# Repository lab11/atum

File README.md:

Atum
====

Atum is a ½ inch² drop-in sensor node module designed to enable rapid
prototyping of wireless embedded devices. The core of Atum is a CC2538
SoC with an Arm Cortex M3 and 802.15.4 radio. Atum also includes an
antenna, 512 bytes of non-volatile FRAM memory, an RTC, and a tri-color LED.

Atum is designed to have two different usage patterns. First, three sides
of the device have castellated headers allowing Atum to be directly
soldered onto a carrier PCB. Atum handles all of the computation and
communication while the carrier board supplies power and attaches
sensors or other peripherals. In the second option, Atum can function
as a complete sensor node. On the bottom are pads for a 3.3 V regulator
and a battery. If needed, a peripheral or sensor board can be stacked on
top using the headers as a bridge.

History
-------

Atum is the spiritual successor to
[Epic](http://www.cs.berkeley.edu/~prabal/projects/epic/). It is slightly
smaller, replaces flash with FRAM, adds an RTC, and includes an antenna.
Epic was designed to be highly flexible while still providing the
components that are common on many sensor platforms. In practice, however,
I noticed that only a small subset of the common features were regularly
used and that Epic carrier boards often repeated the same designs. Atum
tries to address this by providing a simplified interface that provides
the features (e.g. SPI, I2C, ADC, GPIO) that sensor boards need.

Name
----

The spelling "Atum" is taken from the ancient Egyptian god of creation,
but finds better connections as a misspelling of "atom", a core building
block of matter, and as the conjoined words "at" and "UM", as Atum
was developed at the University of Michigan.

Usage
-----

The [Contiki](https://github.com/contiki-os/contiki) operating system
supports the CC2538 and this repository contains a Contiki platform
for Atum. The Contiki platform provides drivers for the peripherals
on Atum and their wiring to the CC2538. See `CONTIKI.md` for more info.

PCB
---

Atum is currently pannelized 40 to a panel. They are designed to be 1mm thick
with castellations on the edge. See `hardware/atum` for board files and
gerbers.

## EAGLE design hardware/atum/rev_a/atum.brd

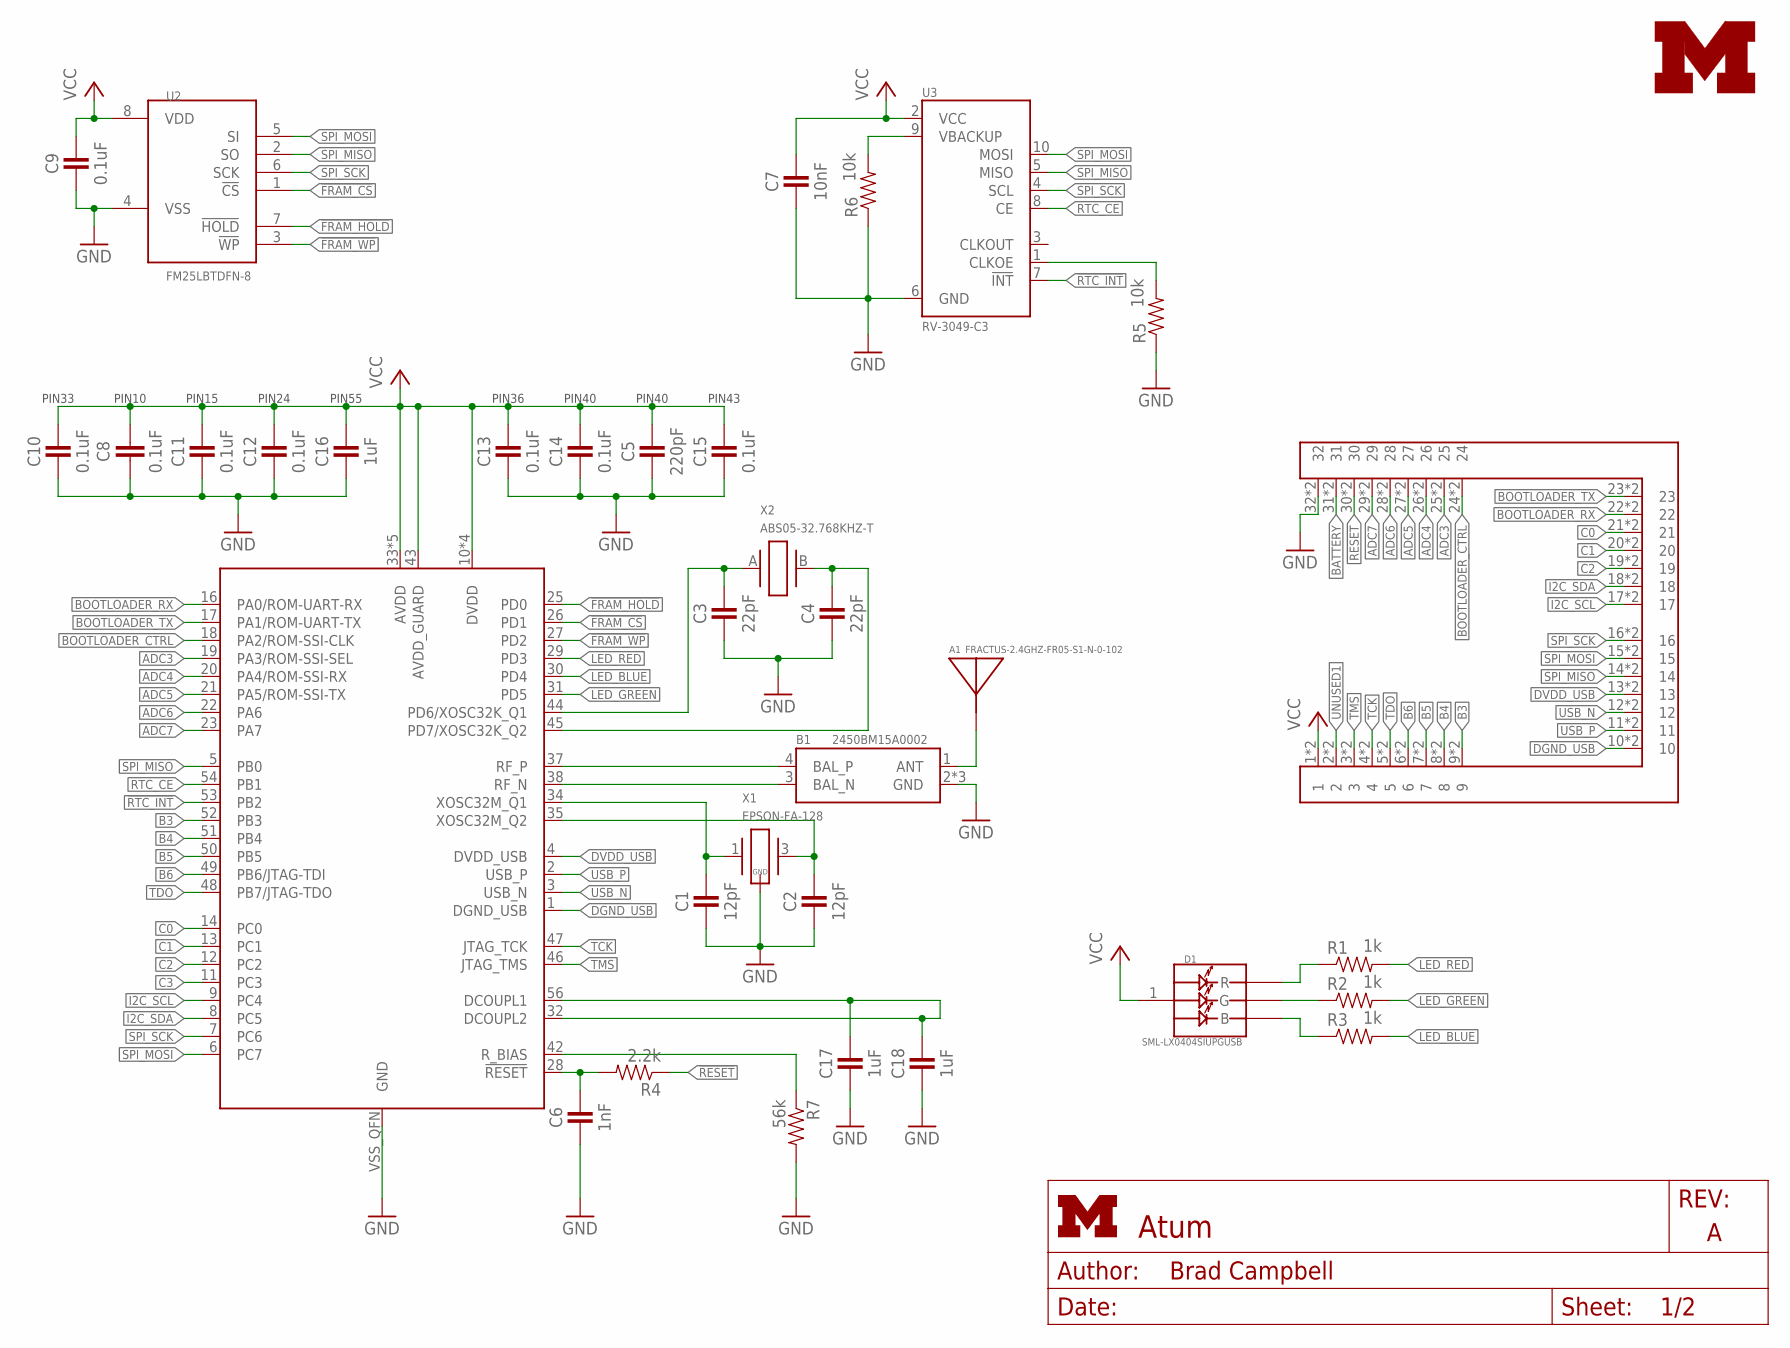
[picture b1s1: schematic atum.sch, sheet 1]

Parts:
A1: FRACTUS-2.4GHZ-FR05-S1-N-0-102; FRACTUS-ANTENNA-FR05-S1-N-0-102
B1: 2450BM15A0002; 2450BM
C1, C2: 12pF; 0402_CAP
C3, C4: 22pF; 0402_CAP
C5: 220pF; 0402_CAP
C6: 1nF; 0402_CAP
C7: 10nF; 0402_CAP
C8: 0.1uF; C0201
C9, C10, C11, C12, C13, C14, C15: 0.1uF; 0402_CAP
C16, C17, C18: 1uF; 0402_CAP
D1: SML-LX0404SIUPGUSB; 1MM_SQ_4PAD
J3: ATUM-HEADER
LOGO1: UMICH_SOLID_TINY; UMICH_SOLID_50MIL
R1, R2, R3: 1k; 0402_RES
R4: 2.2k; 0402_RES
R5, R6: 10k; 0402_RES
R7: 56k; 0402_RES
U1: CC2538; S-PVQFN-N56
U2: FM25LBTDFN-8; TDFN-8; DIGIKEY FM25L04B-DGRA-ND
U3: RV-3049-C3; MICRO-CRYSTAL-C3
X1: EPSON-FA-128; FA-128
X2: ABS05-32.768KHZ-T; ABS05

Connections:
!FRAM_CS: U1.26 (PD1), U2.1 (!CS)
!FRAM_HOLD: U1.25 (PD0), U2.7 (!HOLD)
!FRAM_WP: U1.27 (PD2), U2.3 (!WP)
!RESET: J3.30, J3.30B (30), R4.1
!RTC_INT: U1.53 (PB2), U3.7 (!INT)
ADC3: J3.25, J3.25B (25), U1.19 (PA3/ROM-SSI-SEL)
ADC4: J3.26, J3.26B (26), U1.20 (PA4/ROM-SSI-RX)
ADC5: J3.27, J3.27B (27), U1.21 (PA5/ROM-SSI-TX)
ADC6: J3.28, J3.28B (28), U1.22 (PA6)
ADC7: J3.29, J3.29B (29), U1.23 (PA7)
ANTENNA: A1.1, B1.1 (ANT)
B3: J3.9, J3.9B (9), U1.52 (PB3)
B4: J3.8, J3.8B (8), U1.51 (PB4)
B5: J3.7, J3.7B (7), U1.50 (PB5)
B6: J3.6, J3.6B (6), U1.49 (PB6/JTAG-TDI)
BATTERY: J3.31, J3.31B (31); also elsewhere on the board
BOOTLOADER_CTRL: J3.24, J3.24B (24), U1.18 (PA2/ROM-SSI-CLK)
BOOTLOADER_RX: J3.22, J3.22B (22), U1.16 (PA0/ROM-UART-RX)
BOOTLOADER_TX: J3.23, J3.23B (23), U1.17 (PA1/ROM-UART-TX)
C0: J3.21, J3.21B (21), U1.14 (PC0)
C1: J3.20, J3.20B (20), U1.13 (PC1)
C2: J3.19, J3.19B (19), U1.12 (PC2)
C3: U1.11 (PC3)
DGND_USB: J3.10, J3.10B (10), U1.1 (DGND_USB)
DVDD_USB: J3.13, J3.13B (13), U1.4 (DVDD_USB)
GND: B1.2 (GND), B1.5 (GND), B1.6 (GND), C1.2, C2.2, C3.2, C4.2, C5.2, C6.2, C7.2, C8.2, C9.2, C10.2, C11.2, C12.2, C13.2, C14.2, C15.2, C16.2, C17.2, C18.2, J3.32, J3.32B (32), R5.1, R6.1, R7.2, U1.VSS_QFN (GND), U2.4 (VSS), U3.6 (GND), X1.2 (GND), X1.4 (GND); also elsewhere on the board
I2C_SCL: J3.17, J3.17B (17), U1.9 (PC4)
I2C_SDA: J3.18, J3.18B (18), U1.8 (PC5)
LED_BLUE: R3.2, U1.30 (PD4)
LED_GREEN: R2.2, U1.31 (PD5)
LED_RED: R1.2, U1.29 (PD3)
unnamed: C6.1, R4.2, U1.28 (!RESET)
unnamed: C3.1, U1.44 (PD6/XOSC32K_Q1), X2.A (1)
unnamed: D1.2 (R), R1.1
unnamed: R7.1, U1.42 (R_BIAS)
unnamed: C1.1, U1.34 (XOSC32M_Q1), X1.1
unnamed: C2.1, U1.35 (XOSC32M_Q2), X1.3 (2)
unnamed: D1.4 (G), R2.1
unnamed: D1.3 (B), R3.1
unnamed: C4.1, U1.45 (PD7/XOSC32K_Q2), X2.B (2)
unnamed: R6.2, U3.9 (VBACKUP)
unnamed: C17.1, C18.1, U1.32 (DCOUPL2), U1.56 (DCOUPL1)
unnamed: R5.2, U3.1 (CLKOE)
RF_N: B1.3 (BAL_N), U1.38 (RF_N)
RF_P: B1.4 (BAL_P), U1.37 (RF_P)
RTC_CE: U1.54 (PB1), U3.8 (CE)
SPI_MISO: J3.14, J3.14B (14), U1.5 (PB0), U2.2 (SO), U3.5 (MISO)
SPI_MOSI: J3.15, J3.15B (15), U1.6 (PC7), U2.5 (SI), U3.10 (MOSI)
SPI_SCK: J3.16, J3.16B (16), U1.7 (PC6), U2.6 (SCK), U3.4 (SCL)
TCK: J3.4, J3.4B (4), U1.47 (JTAG_TCK)
TDO: J3.5, J3.5B (5), U1.48 (PB7/JTAG-TDO)
TMS: J3.3, J3.3B (3), U1.46 (JTAG_TMS)
UNUSED1: J3.2, J3.2B (2)
USB_N: J3.12, J3.12B (12), U1.3 (USB_N)
USB_P: J3.11, J3.11B (11), U1.2 (USB_P)
VCC: C5.1, C7.1, C8.1, C9.1, C10.1, C11.1, C12.1, C13.1, C14.1, C15.1, C16.1, D1.1 (VDD), J3.1, J3.1B (1), U1.10 (DVDD), U1.15 (DVDD), U1.24 (DVDD), U1.33 (AVDD), U1.36 (AVDD), U1.39 (AVDD), U1.40 (AVDD), U1.41 (AVDD), U1.43 (AVDD_GUARD), U1.55 (DVDD), U2.8 (VDD), U3.2 (VCC); also elsewhere on the board

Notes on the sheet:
PIN10
PIN15
PIN24
PIN55
PIN33
PIN36
PIN40
PIN43

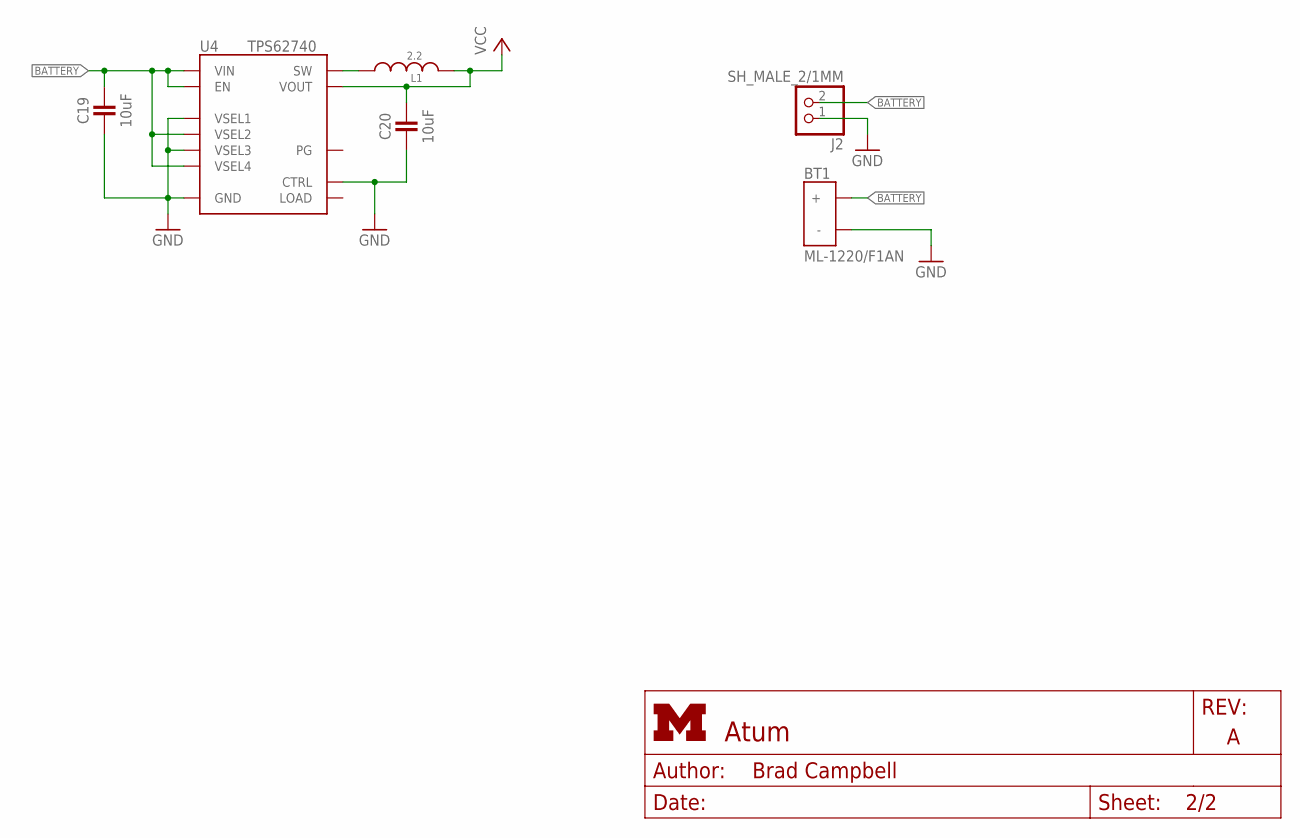
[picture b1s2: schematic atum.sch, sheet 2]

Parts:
BT1: ML-1220/F1AN; ML-1220/F1BN
C19, C20: 10uF; 0603_CAP; DIGIKEY 490-7316-1-ND
J2: SH_MALE_2/1MM; SH-1X2/1MM
L1: 2.2; MIPSZ201D
U4: TPS62740; R-PWSON-12

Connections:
BATTERY: BT1.POS (+), C19.1, J2.2, U4.1 (VIN), U4.8 (VSEL4), U4.10 (VSEL2), U4.12 (EN); also elsewhere on the board
GND: BT1.NEG (-), C19.2, C20.2, J2.1, U4.3 (GND), U4.4 (CTRL), U4.9 (VSEL3), U4.11 (VSEL1), U4.NC (GND); also elsewhere on the board
unnamed: L1.1, U4.2 (SW)
VCC: C20.1, L1.2, U4.5 (VOUT); also elsewhere on the board

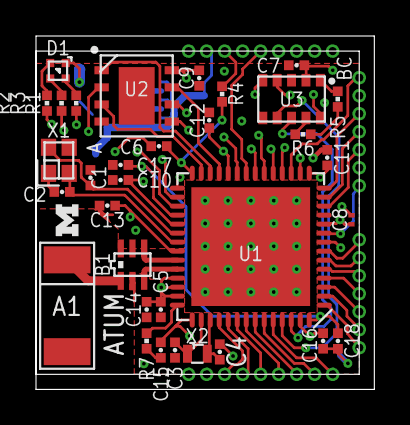
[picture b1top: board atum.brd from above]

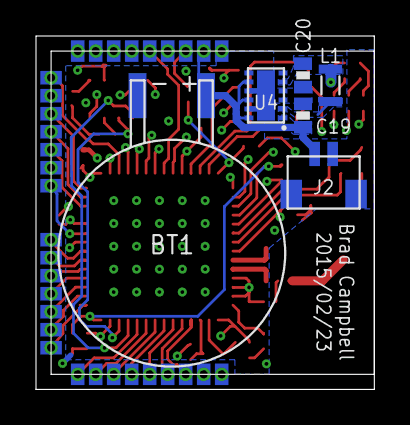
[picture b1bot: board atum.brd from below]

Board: 4 copper layers, 18.8 x 19.6 mm, 41 parts (6 on the bottom side), 56 nets.

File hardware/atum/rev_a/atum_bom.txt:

# Bill of Materials
# Converted from atum_bom.xlsx
# Generated by bom_to_text.py

Qty  Value                           Device                          Package                          Parts                             Description                                                   DIGIKEY           MOUSER               NEWARK   RICHARDSON_RFPD
1    FRACTUS-2.4GHZ-FR05-S1-N-0-102  FRACTUS-2.4GHZ-FR05-S1-N-0-102  FRACTUS-ANTENNA-FR05-S1-N-0-102  A1                                Fractus Compact Reach XtendTM chip antenna                                                                    FR05-S1-N-0102B
1    2450BM15A0002                   2450BM15A0002                   2450BM                           B1                                BALUN JTI MATCHED ZIGBEE                                      712-1536-1-ND     609-2450BM15A0002E   41T1684  
1    ML-1220/F1AN                    ML-1220/F1AN                    ML-1220/F1BN                     BT1                               BATTERY LITH 3V RECHARGE PC PINS                              P663-ND           658-ML-1220/F1BN              
2    12pF                            CAPACITOR                       0402_CAP                         C1, C2                            0402 Capacitor                                                445-1236-1-ND                          90R7560  
2    22pF                            CAPACITOR                       0402_CAP                         C3, C4                            0402 Capacitor                                                490-5868-1-ND                          48W5745  
1    220pF                           CAPACITOR                       0402_CAP                         C5                                0402 Capacitor                                                445-1251-1-ND                          55T0065  
1    1nF                             CAPACITOR                       0402_CAP                         C6                                0402 Capacitor                                                445-2651-1-ND                          90R7554  
1    10nF                            CAPACITOR                       0402_CAP                         C7                                0402 Capacitor                                                445-1260-1-ND                          90R7604  
1    0.1uF                           C-EUC0201                       0201_CAP                         C8                                0201 Capacitor                                                445-1796-1-ND                          90R7553  
7    0.1uF                           CAPACITOR                       0402_CAP                         C9, C10, C11, C12, C13, C14, C15  0402 Capacitor                                                445-1265-1-ND                          87R3259  
3    1uF                             CAPACITOR                       0402_CAP                         C16, C17, C18                     0402 Capacitor                                                445-4998-1-ND                          90R7580  
2    10uF                            CAPACITOR0603_CAP               0603_CAP                         C19, C20                          CAP CER 10UF 6.3V 20% X5R 0603                                490-7316-1-ND                                   
1    SML-LX0404SIUPGUSB              SML-LX0404SIUPGUSB              1MM_SQ_4PAD                      D1                                1mm^2 RGB LED                                                 67-2125-1-ND      696-LX0404SIUPGUSB   23T0583  
1    ATUM-HEADER                     ATUM-HEADER                     ATUM-HEADER                      J1                                                                                                                                              
1    SH_MALE_2/1MM                   SH_MALE_2/1MM                   SH-1X2/1MM                       J2                                1.0mm pitch/Disconnectable Crimp style connectors             455-1788-2-ND                          26P0950  
1    2.2uH                           MIPSZ2012D                      MIPSZ201D                        L1                                FDK Multi-layer Power Inductor (Very Small Type)                                                              
3    1k                              RESISTOR                        0402_RES                         R1, R2, R3                        Resistor                                                      RHM1.0KCECT-ND                                  
1    2.2k                            RESISTOR                        0402_RES                         R4                                Resistor                                                      RHM2.2KCECT-ND                                  
2    10k                             RESISTOR                        0402_RES                         R5, R6                            Resistor                                                      RHM10KCECT-ND                                   
1    56k                             RESISTOR                        0402_RES                         R7                                Resistor                                                      RHM56KBHCT-ND                                   
1    CC2538                          CC2538                          S-PVQFN-N56                      U1                                A Powerful System-On-Chip for 2.4-GHz IEEE 802.15.4, 6LoWPAN  296-35797-1-ND    595-CC2538SF53RTQT   87W7713  
1    FM25LBTDFN-8                    FM25LBTDFN-8                    TDFN-8                           U2                                IC FRAM 4KBIT 10MHZ 8SOIC                                     FM25L04B-DGRA-ND  877-FM25L04B-DG               
1    RV-3049-C3                      RV-3049-C3                      MICRO-CRYSTAL-C3                 U3                                Ultra miniature Real-Time-Clock Module                                                               09X0513  
1    TPS62740                        TPS62740                        R-PWSON-12                       U4                                360nA Step Down Converter for Low Power Applications          296-37134-1-ND    595-TPS62740DSST     27X9745  
1    EPSON-FA-128                    EPSON-FA-128                    FA-128                           X1                                MHz RANGE CRYSTAL UNIT                                        SER3800CT-ND      732-FA128-32F20X-K3           
1    ABS05-32.768KHZ-T               ABS05-32.768KHZ-T               ABS05                            X2                                32.768kHz Crystal                                             535-11899-1-ND    815-ABS05-32.768K-T  24W8430

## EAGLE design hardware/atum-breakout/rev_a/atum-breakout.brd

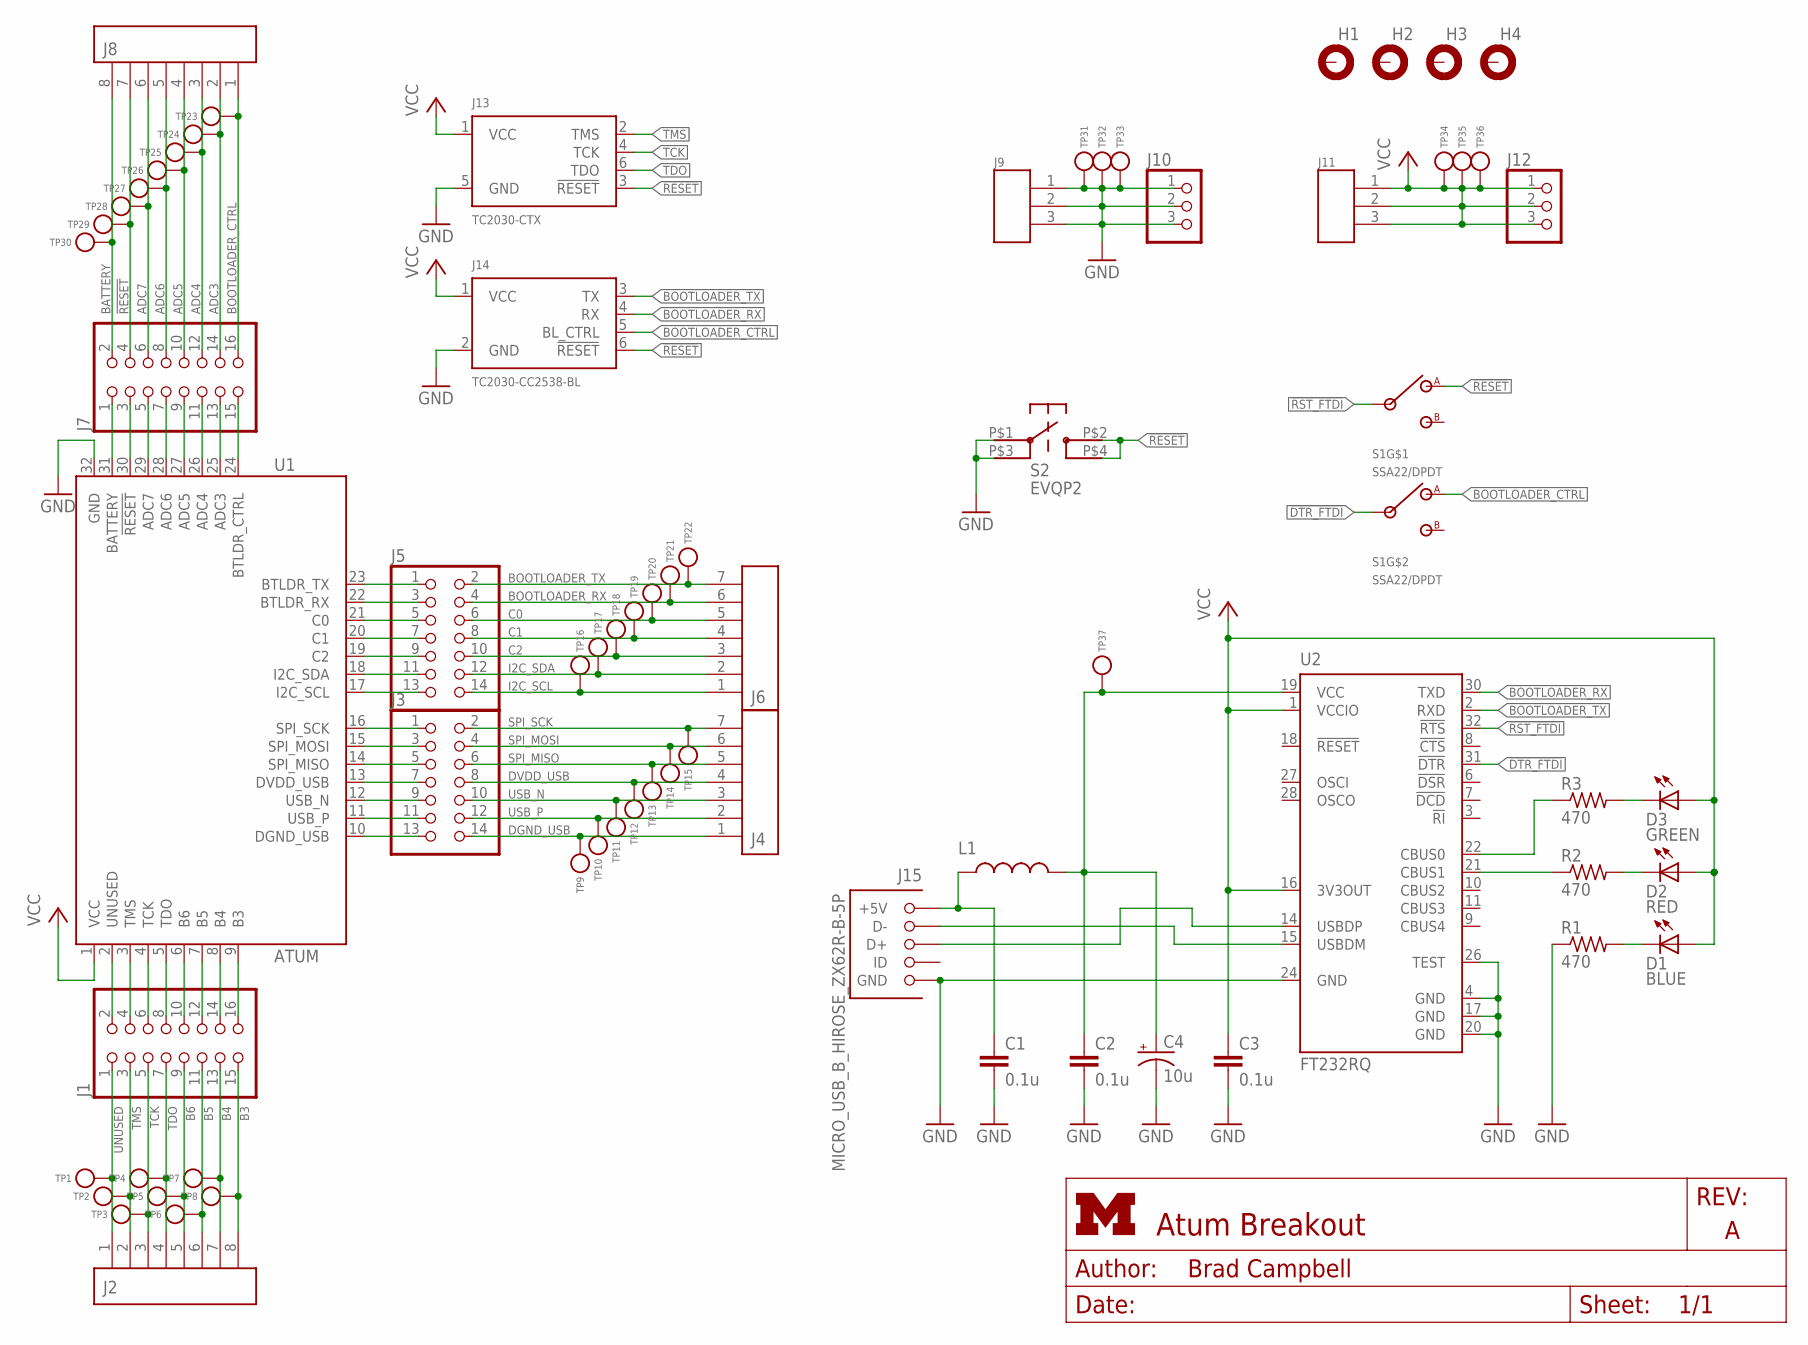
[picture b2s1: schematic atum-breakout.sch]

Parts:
C1, C2, C3: 0.1u; C0603; DIGIKEY 445-1316-1-ND
C4: 10u; EIA3216; DIGIKEY 478-1655-1-ND
D1: BLUE; LED-0603
D2: RED; LED-0603
D3: GREEN; LED-0603
H1, H2, H3, H4: MOUNT-PAD-ROUND3.2; 3,2-PAD
J1, J7: PINHD-2X8; 2X08; DIGIKEY 609-3364-ND
J2, J8: SCREW-TERMINAL_8_0.100; CONN_BLOCK_8
J3, J5: PINHD-2X7; 2X07; DIGIKEY 609-3491-ND
J4, J6: SCREW-TERMINAL_7_0.100; CONN_BLOCK_7
J9, J11: SCREW-TERMINAL_3_0.100; CONN_BLOCK_3
J10, J12: PINHD-1X3; 1X03
J13: TC2030-CTX; TC2030-IDC
J14: TC2030-CC2538-BL; TC2030-IDC
J15: MICRO_USB_B_HIROSE_ZX62R-B-5P; USB_MICRO_B-HIROSE-ZX62R-B-5P; MOUSER 798-ZX62R-B-5P
L1: INDUCTOR0603; 0603; DIGIKEY 240-2373-1-ND
R1, R2, R3: 470; R0603
S1: SSA22/DPDT; DIGIKEY 450-1604-ND
S2: EVQP2; DIGIKEY P11084SCT-ND
TP1, TP2, TP3, TP4, TP5, TP6, TP7, TP8, TP9, TP10, TP11, TP12, TP13, TP14, TP15, TP16, TP17, TP18, TP19, TP20, TP21, TP22, TP23, TP24, TP25, TP26, TP27, TP28, TP29, TP30, TP31, TP32, TP33, TP34, TP35, TP36, TP37: TEST_POINT_0.040IN; TESTPOINT_0.040IN
U1: ATUM
U2: FT232RQ; QFN32; DIGIKEY 768-1008-1-ND

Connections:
!DTR_FTDI: S1.COM2 (2), U2.31 (!DTR)
!RESET: J7.3, J7.4, J8.7, J13.3 (!RESET), J14.6 (!RESET), S1.A1 (1), S2.P$2, S2.P$4, TP29.TESTPOINT, U1.30 (!RESET)
!RST_FTDI: S1.COM1 (2), U2.32 (!RTS)
ADC3: J7.13, J7.14, J8.2, TP24.TESTPOINT, U1.25 (ADC3)
ADC4: J7.11, J7.12, J8.3, TP25.TESTPOINT, U1.26 (ADC4)
ADC5: J7.9, J7.10, J8.4, TP26.TESTPOINT, U1.27 (ADC5)
ADC6: J7.7, J7.8, J8.5, TP27.TESTPOINT, U1.28 (ADC6)
ADC7: J7.5, J7.6, J8.6, TP28.TESTPOINT, U1.29 (ADC7)
B3: J1.15, J1.16, J2.8, TP8.TESTPOINT, U1.9 (B3)
B4: J1.13, J1.14, J2.7, TP7.TESTPOINT, U1.8 (B4)
B5: J1.11, J1.12, J2.6, TP6.TESTPOINT, U1.7 (B5)
B6: J1.9, J1.10, J2.5, TP5.TESTPOINT, U1.6 (B6)
BATTERY: J7.1, J7.2, J8.8, TP30.TESTPOINT, U1.31 (BATTERY)
BOOTLOADER_CTRL: J7.15, J7.16, J8.1, J14.5 (BL_CTRL), S1.A2 (1), TP23.TESTPOINT, U1.24 (BTLDR_CTRL)
BOOTLOADER_RX: J5.3, J5.4, J6.6, J14.4 (RX), TP21.TESTPOINT, U1.22 (BTLDR_RX), U2.30 (TXD)
BOOTLOADER_TX: J5.1, J5.2, J6.7, J14.3 (TX), TP22.TESTPOINT, U1.23 (BTLDR_TX), U2.2 (RXD)
C0: J5.5, J5.6, J6.5, TP20.TESTPOINT, U1.21 (C0)
C1: J5.7, J5.8, J6.4, TP19.TESTPOINT, U1.20 (C1)
C2: J5.9, J5.10, J6.3, TP18.TESTPOINT, U1.19 (C2)
DGND_USB: J3.13, J3.14, J4.1, TP9.TESTPOINT, U1.10 (DGND_USB)
DVDD_USB: J3.7, J3.8, J4.4, TP12.TESTPOINT, U1.13 (DVDD_USB)
GND: C1.2, C2.2, C3.2, C4.C (-), J9.1, J9.2, J9.3, J10.1, J10.2, J10.3, J13.5 (GND), J14.2 (GND), J15.5 (GND), R1.1, S2.P$1, S2.P$3, TP31.TESTPOINT, TP32.TESTPOINT, TP33.TESTPOINT, U1.32 (GND), U2.4 (GND), U2.17 (GND), U2.20 (GND), U2.24 (GND), U2.26 (TEST)
I2C_SCL: J5.13, J5.14, J6.1, TP16.TESTPOINT, U1.17 (I2C_SCL)
I2C_SDA: J5.11, J5.12, J6.2, TP17.TESTPOINT, U1.18 (I2C_SDA)
unnamed: R3.1, U2.22 (CBUS0)
unnamed: D2.C, R2.2
unnamed: J15.2 (D-), U2.15 (USBDM)
unnamed: J15.3 (D+), U2.14 (USBDP)
unnamed: R2.1, U2.21 (CBUS1)
unnamed: C2.1, C4.A (+), L1.2, TP37.TESTPOINT, U2.19 (VCC)
unnamed: D3.C, R3.2
unnamed: D1.C, R1.2
SPI_MISO: J3.5, J3.6, J4.5, TP13.TESTPOINT, U1.14 (SPI_MISO)
SPI_MOSI: J3.3, J3.4, J4.6, TP14.TESTPOINT, U1.15 (SPI_MOSI)
SPI_SCK: J3.1, J3.2, J4.7, TP15.TESTPOINT, U1.16 (SPI_SCK)
TCK: J1.5, J1.6, J2.3, J13.4 (TCK), TP3.TESTPOINT, U1.4 (TCK)
TDO: J1.7, J1.8, J2.4, J13.6 (TDO), TP4.TESTPOINT, U1.5 (TDO)
TMS: J1.3, J1.4, J2.2, J13.2 (TMS), TP2.TESTPOINT, U1.3 (TMS)
UNUSED: J1.1, J1.2, J2.1, TP1.TESTPOINT, U1.2 (UNUSED)
USB5V: C1.1, J15.1 (+5V), L1.1
USB_N: J3.9, J3.10, J4.3, TP11.TESTPOINT, U1.12 (USB_N)
USB_P: J3.11, J3.12, J4.2, TP10.TESTPOINT, U1.11 (USB_P)
VCC: C3.1, D1.A, D2.A, D3.A, J11.1, J11.2, J11.3, J12.1, J12.2, J12.3, J13.1 (VCC), J14.1 (VCC), TP34.TESTPOINT, TP35.TESTPOINT, TP36.TESTPOINT, U1.1 (VCC), U2.1 (VCCIO), U2.16 (3V3OUT)

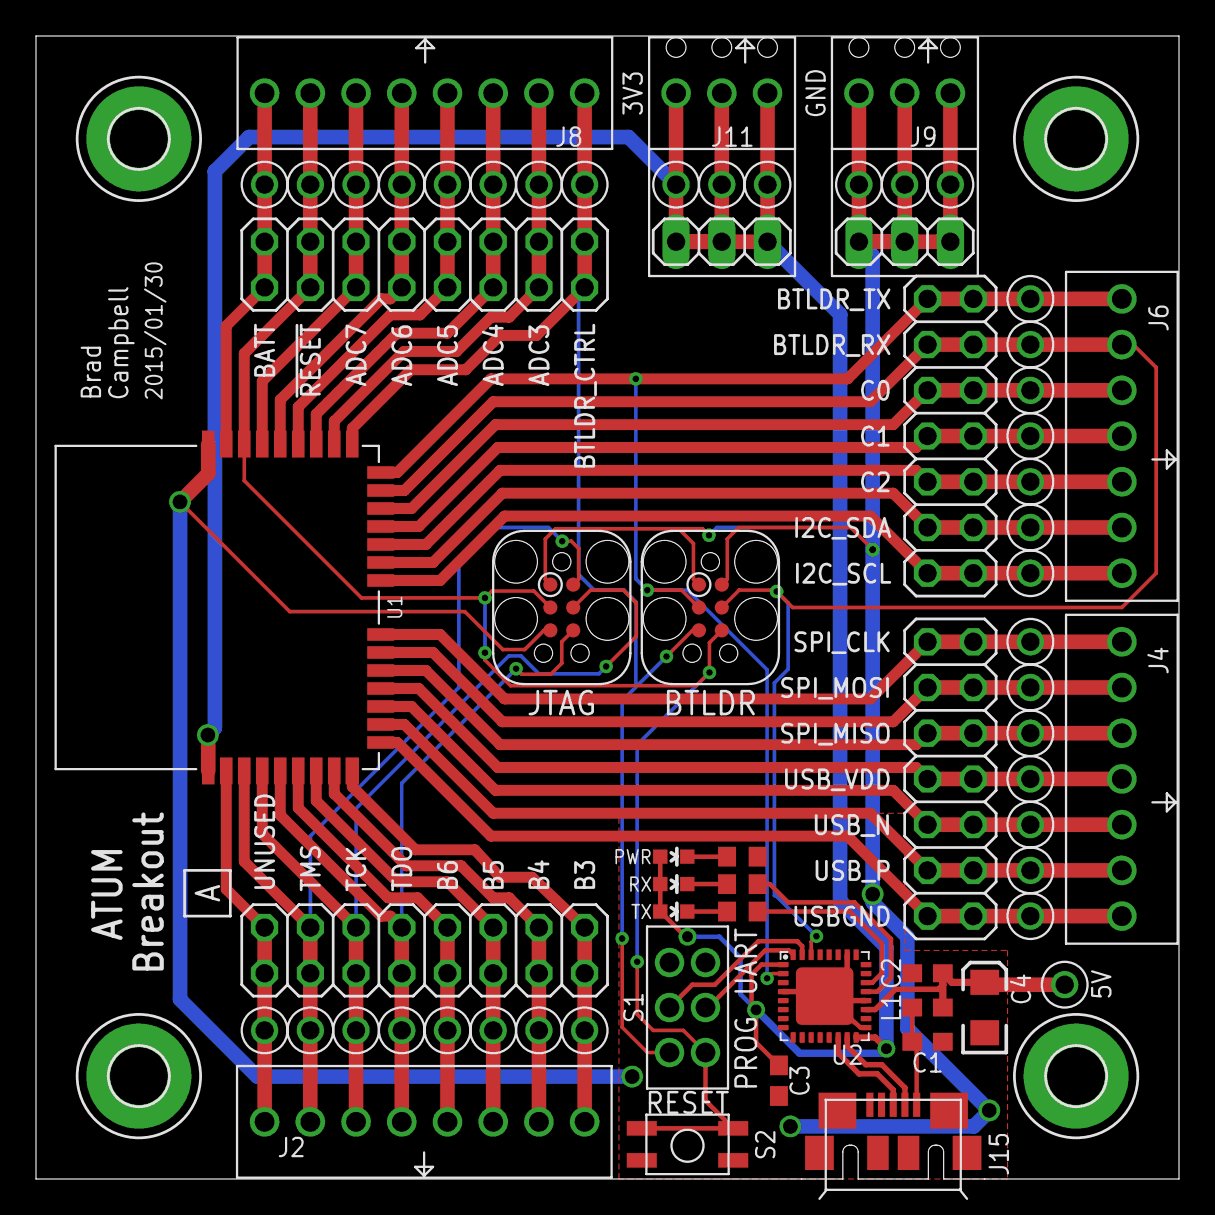
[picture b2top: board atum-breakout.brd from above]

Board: 2 copper layers, 63.5 x 63.5 mm, 71 parts (0 on the bottom side), 43 nets.

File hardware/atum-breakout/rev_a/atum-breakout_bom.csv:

# Bill of Materials
# Converted from atum-breakout_bom.xlsx
# Generated by bom_to_text.py

Qty,Value,Device,Package,Parts,Description,DIGIKEY,MOUSER,NEWARK
3,0.1u,C-EUC0603,C0603,"C1, C2, C3","CAPACITOR, European symbol",445-1316-1-ND,810-C1608X7R1E104K,
1,10u,CAP_POL1206,EIA3216,C4,Capacitor Polarized,478-1655-1-ND,581-TAJA106K016R,
1,BLUE,LED0603,LED-0603,D1,LEDs,,,
1,RED,LED0603,LED-0603,D2,LEDs,,,
1,GREEN,LED0603,LED-0603,D3,LEDs,,,
2,,PINHD-2X8,2X08,"J1, J7",PIN HEADER,609-3364-ND,649-68602-116HLF,20M2833
2,SCREW-TERMINAL_8_0.100,SCREW-TERMINAL_8_0.100,CONN_BLOCK_8,"J2, J8",8x 0.100 in screw terminal block,277-1279-ND,651-1725711,71C4111
2,,PINHD-2X7,2X07,"J3, J5",PIN HEADER,609-3491-ND,649-67996-114HLF,30M1973
2,SCREW-TERMINAL_7_0.100,SCREW-TERMINAL_7_0.100,CONN_BLOCK_7,"J4, J6",7x 0.100 in screw terminal block,277-1278-ND,651-1725708,14X4980
2,SCREW-TERMINAL_3_0.100,SCREW-TERMINAL_3_0.100,CONN_BLOCK_3,"J9, J11",3x 0.100 in screw terminal block,277-1274-ND,651-1725669,71C4108
2,,PINHD-1X3,1X03,"J10, J12",PIN HEADER,609-3461-ND,649-68000-103HLF,88K1775
1,MICRO_USB_B_HIROSE_ZX62R-B-5P,MICRO_USB_B_HIROSE_ZX62R-B-5P,USB_MICRO_B-HIROSE-ZX62R-B-5P,J15,USB Micro B Connector,H11574CT-ND,798-ZX62R-B-5P,69W0714
1,,INDUCTOR0603,L0603,L1,Inductors,240-2373-1-ND,875-MI0603K300R-10,
3,470,R-US_R0603,R0603,"R1, R2, R3","RESISTOR, American symbol",,,
1,SSA22/DPDT,SSA22/DPDT,SSA22/DPDT,S1,SW SLIDE DPDT 2POS SSA SER 30V,450-1604-ND,506-SSA22,50F5561
1,EVQP2,EVQP2,EVQP2,S2,,P11084SCT-ND,667-EVQ-P2K02Q,
37,TEST_POINT_0.040IN,TEST_POINT_0.040IN,TESTPOINT_0.040IN,TP1-TP37,0.040in Test Point,5001K-ND,534-5001,
1,ATUM,ATUM,ATUM,U1,Atum sensorboard prototyping module.,,,
1,FT232RQ,FT232RQ,QFN32,U2,FTDI USB,768-1008-1-ND,895-FT232RQ,91K9919

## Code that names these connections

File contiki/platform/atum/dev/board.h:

/*
 * Copyright (c) 2012, Texas Instruments Incorporated - http://www.ti.com/
 * All rights reserved.
 *
 * Redistribution and use in source and binary forms, with or without
 * modification, are permitted provided that the following conditions
 * are met:
 * 1. Redistributions of source code must retain the above copyright
 *    notice, this list of conditions and the following disclaimer.
 * 2. Redistributions in binary form must reproduce the above copyright
 *    notice, this list of conditions and the following disclaimer in the
 *    documentation and/or other materials provided with the distribution.
 *
 * 3. Neither the name of the copyright holder nor the names of its
 *    contributors may be used to endorse or promote products derived
 *    from this software without specific prior written permission.
 *
 * THIS SOFTWARE IS PROVIDED BY THE COPYRIGHT HOLDERS AND CONTRIBUTORS
 * ``AS IS'' AND ANY EXPRESS OR IMPLIED WARRANTIES, INCLUDING, BUT NOT
 * LIMITED TO, THE IMPLIED WARRANTIES OF MERCHANTABILITY AND FITNESS
 * FOR A PARTICULAR PURPOSE ARE DISCLAIMED.  IN NO EVENT SHALL THE
 * COPYRIGHT HOLDER OR CONTRIBUTORS BE LIABLE FOR ANY DIRECT, INDIRECT,
 * INCIDENTAL, SPECIAL, EXEMPLARY, OR CONSEQUENTIAL DAMAGES
 * (INCLUDING, BUT NOT LIMITED TO, PROCUREMENT OF SUBSTITUTE GOODS OR
 * SERVICES; LOSS OF USE, DATA, OR PROFITS; OR BUSINESS INTERRUPTION)
 * HOWEVER CAUSED AND ON ANY THEORY OF LIABILITY, WHETHER IN CONTRACT,
 * STRICT LIABILITY, OR TORT (INCLUDING NEGLIGENCE OR OTHERWISE)
 * ARISING IN ANY WAY OUT OF THE USE OF THIS SOFTWARE, EVEN IF ADVISED
 * OF THE POSSIBILITY OF SUCH DAMAGE.
 */
/** \addtogroup cc2538
 * @{
 *
 * \defgroup cc2538-smartrf SmartRF06EB Peripherals
 *
 * Defines related to the SmartRF06EB
 *
 * This file provides connectivity information on LEDs, Buttons, UART and
 * other SmartRF peripherals
 *
 * Notably, PC0 is used to drive LED1 as well as the USB D+ pullup. Therefore
 * when USB is enabled, LED1 can not be driven by firmware.
 *
 * This file can be used as the basis to configure other platforms using the
 * cc2538 SoC.
 * @{
 *
 * \file
 * Header file with definitions related to the I/O connections on the TI
 * SmartRF06EB
 *
 * \note   Do not include this file directly. It gets included by contiki-conf
 *         after all relevant directives have been set.
 */
#ifndef BOARD_H_
#define BOARD_H_

#include "dev/gpio.h"
#include "dev/nvic.h"
/*---------------------------------------------------------------------------*/
/** \name SmartRF LED configuration
 *
 * LEDs on the SmartRF06 (EB and BB) are connected as follows:
 * - LED1 (Red)    -> PC0
 * - LED2 (Yellow) -> PC1
 * - LED3 (Green)  -> PC2
 * - LED4 (Orange) -> PC3
 *
 * LED1 shares the same pin with the USB pullup
 * @{
 */
/*---------------------------------------------------------------------------*/
/* Some files include leds.h before us, so we need to get rid of defaults in
 * leds.h before we provide correct definitions */
#undef LEDS_GREEN
#undef LEDS_BLUE
#undef LEDS_RED
#undef LEDS_CONF_ALL

#define LEDS_BLUE                16 /**< PD4 */
#define LEDS_RED                 8  /**< PD3 */
#define LEDS_GREEN               32 /**< PD5 */
#define LEDS_CONF_ALL            56

/* Notify various examples that we have LEDs */
#define PLATFORM_HAS_LEDS        1

#define LED_BLUE_BASE            GPIO_D_BASE
#define LED_RED_BASE             GPIO_D_BASE
#define LED_GREEN_BASE           GPIO_D_BASE
#define LED_BLUE_MASK            GPIO_PIN_MASK(4)
#define LED_RED_MASK             GPIO_PIN_MASK(3)
#define LED_GREEN_MASK           GPIO_PIN_MASK(5)
/** @} */
/*---------------------------------------------------------------------------*/
/** \name USB configuration
 *
 * The USB pullup is driven by PC0 and is shared with LED1
 */
#define USB_PULLUP_PORT          GPIO_C_NUM
#define USB_PULLUP_PIN           0
/** @} */
/*---------------------------------------------------------------------------*/
/** \name UART configuration
 *
 * On the SmartRF06EB, the UART (XDS back channel) is connected to the
 * following ports/pins
 * - RX:  PA0
 * - TX:  PA1
 * - CTS: PB0 (Can only be used with UART1)
 * - RTS: PD3 (Can only be used with UART1)
 *
 * We configure the port to use UART0. To use UART1, replace UART0_* with
 * UART1_* below.
 * @{
 */
#define UART0_RX_PORT            GPIO_A_NUM
#define UART0_RX_PIN             0

#define UART0_TX_PORT            GPIO_A_NUM
#define UART0_TX_PIN             1
// unused uart1
#define UART1_CTS_PORT           GPIO_C_NUM
#define UART1_CTS_PIN            1

#define UART1_RTS_PORT           GPIO_C_NUM
#define UART1_RTS_PIN            2
/** @} */


#define DW1000_CS_N_PORT_NUM   GPIO_C_NUM
#define DW1000_CS_N_PIN        0
#define DW1000_IRQ_PORT_NUM    GPIO_C_NUM
#define DW1000_IRQ_PIN         1
#define DW1000_RST_N_PORT_NUM  GPIO_B_NUM
#define DW1000_RST_N_PIN       3



/*---------------------------------------------------------------------------*/
/**
 * \name FM25L04B configuration
 *
 * These values configure which CC2538 pins to use for the FRAM chip.
 * @{
 */
#define FM25L04B_SPI_BUS         0
#define FM25L04B_HOLD_N_PORT_NUM GPIO_D_NUM
#define FM25L04B_HOLD_N_PIN      0
#define FM25L04B_WP_N_PORT_NUM   GPIO_D_NUM
#define FM25L04B_WP_N_PIN        2
#define FM25L04B_CS_N_PORT_NUM   GPIO_D_NUM
#define FM25L04B_CS_N_PIN        1
/** @} */
/*---------------------------------------------------------------------------*/
/**
 * \name RV-3049-C3 configuration
 *
 * These values configure which CC2538 pins to use for the RTC chip.
 * @{
 */
#define RV3049_INT_N_PORT_NUM    GPIO_B_NUM
#define RV3049_INT_N_PIN         2
#define RV3049_CS_PORT_NUM       GPIO_B_NUM
#define RV3049_CS_PIN            1
/** @} */
/*---------------------------------------------------------------------------*/
/**
 * \name ADC configuration
 *
 * These values configure which CC2538 pins and ADC channels to use for the ADC
 * inputs.
 *
 * ADC inputs can only be on port A.
 * @{
 */
#define ADC_ALS_PWR_PORT         GPIO_A_NUM /**< ALS power GPIO control port */
#define ADC_ALS_PWR_PIN          7 /**< ALS power GPIO control pin */
#define ADC_ALS_OUT_PIN          6 /**< ALS output ADC input pin on port A */
/** @} */
/*---------------------------------------------------------------------------*/
/**
 * \name SPI configuration
 *
 * These values configure which CC2538 pins to use for the SPI lines.
 * @{
 */
// #define SPI0_CLK_PORT             GPIO_C_NUM
// #define SPI0_CLK_PIN              6
// #define SPI0_MOSI_PORT            GPIO_C_NUM
// #define SPI0_MOSI_PIN             7
// #define SPI0_MISO_PORT            GPIO_B_NUM
// #define SPI0_MISO_PIN             0
#define SPI0_CLK_PORT             GPIO_C_NUM
#define SPI0_CLK_PIN              6
#define SPI0_TX_PORT            GPIO_C_NUM
#define SPI0_TX_PIN             7
#define SPI0_RX_PORT            GPIO_B_NUM
#define SPI0_RX_PIN             0
/** @} */
/*---------------------------------------------------------------------------*/
/**
 * \name I2C configuration
 *
 * These values configure which CC2538 pins to use for the I2C lines.
 * @{
 */
#define I2C_SDA_PORT            GPIO_C_NUM
#define I2C_SDA_PIN             5
#define I2C_SCL_PORT            GPIO_C_NUM
#define I2C_SCL_PIN             4
/** @} */
/*---------------------------------------------------------------------------*/
/**
 * \name Device string used on startup
 * @{
 */
#define BOARD_STRING "Atum"
/** @} */

#endif /* BOARD_H_ */

/**
 * @}
 * @}
 */

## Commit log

2014-04-28 renamed myth to atum
2014-04-28 removed myth.info
2014-04-28 remvoed myth zips
2014-04-28 shipped atum
2014-05-08 updated silkscreen and names
    - renumbered parts
    - made silkscreen names for assembly
2014-05-08 added bom
2014-05-08 new publish files for atum
2014-05-25 documentation for atum
2014-05-25 renamed atum eagle library
2014-05-28 add fram driver for atum/contiki
2014-05-28 adding atum platform for contiki
2014-05-28 added remaining bits for platform
2014-05-28 updated makefile for atum
2014-05-28 added blink app
2014-05-28 added fram test for atum
2014-05-28 added simple radio test for atum
2014-05-28 first pass of porting rv3049 driver from tinyos
2014-05-28 updated platform to use rv3049
2014-05-28 new gitignore to remove contiki built output
2014-05-31 updated atum readme
2014-05-31 forgot about the led
2014-05-31 atum
2014-06-02 working on rtc code
2014-06-02 new rtc test app
2014-06-02 add make time script
2014-06-03 moved time script to tools directory
    made executable
2014-06-03 updated rtc driver
2014-06-03 added rtc driver to be compiled every time
    needs updated rtc init values
2014-06-03 updated rtc test app
2014-06-03 changed auto invoke from -i to -k
2014-06-04 created atum breakout board
2014-06-04 eagle gitignore
2014-06-04 updated part labels
2014-06-05 atum breakout bom
2014-06-05 updated breakout bom
2014-06-05 added rev letter and updated date on silkscreen
2014-06-05 added publish files for atum-breakout
2014-06-05 updated gitignore
2014-06-08 trying to improve castellations
2014-06-08 updated atum platform to newest contiki cc2538
2014-06-08 added readme for contiki code
2014-06-08 fixed code formatting in readme
2014-08-02 smaller vias
2014-08-30 change <app>.upload to install
2014-08-30 new atum a
    designed for advanced circuits default stack
2014-08-30 adc test for airflow sensor
2014-12-19 update with latest contiki
2015-01-29 Varried small changes to docs
2015-01-31 updated atum breakout
2015-01-31 old updates to atum zips
2015-01-31 don't need ipv6
2015-02-22 specify make time script
2015-02-22 adding support for decawave dw1000
2015-02-23 made panel for atum
    added fab notes
2015-02-25 added support for specifying which USB port
2015-03-01 get all 3 packets with dw1000
    doesn't do range yet, however...
2015-03-01 get ranges now
2015-03-01 added support for pannelizing atum
2015-03-22 add pricing estimate
2015-03-29 decawave changes
2015-03-29 readme for contiki
2015-03-29 coap leds for setting leds
2015-03-29 remove decawave from atum
2015-03-29 updated atum makefile
2015-04-01 changing 32 kHz source from internal RC to external XO to increase its accuracy
2015-05-15 update atum to remove startup.gcc
    now in cpu/cc2538
2015-05-15 coap leds changes
2015-05-15 committing old nrf51822 interface code
2015-05-15 router app
2015-05-15 faster bsl serial
2015-05-15 trying to nest
2015-05-23 trying things with nested
2015-05-23 add script for making a coap server from serial
2015-05-30 adding the ability to control the watchdog outside of contiki-main
2015-07-02 update to contiki master
2015-11-23 fix rtc test to compile with new contiki
    they fixed their led API problem
2016-06-17 add magnetic mount
2016-08-08 update contiki conf to newest contiki
2016-10-03 add i2c pins to board.h

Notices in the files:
parts and their libraries:
SparkFun: Licensing: CC v3.0 Share-Alike You are welcome to use this library for commercial purposes.
